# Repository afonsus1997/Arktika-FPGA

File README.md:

### Project description

The Arktika FPGA is an open-source FPGA development board based on the ICE40 family (ICE40HX4K-TQ144).

### Main Features:

* 78 total user digital IO pins
  * 18 arduino uno compatible headers
  * 6 PMOD connectors (40 total pins)
    * 2x10pin
    * 2x6pin
    * 2x4pin
  * 18pin additional "EXT" connector
  * Buzzer connector
* 4 analog input channels
  * MCP3204 ADC
* 8 on-board LEDs
* 8 on-board DIP switches
* 4 on-board push buttons
* USB to UART bridge
* 50Mhz active crystal oscillator
* FT232hl USB bridge
  * Used for FPGA or flash programming
  * Breakout header for external use

### Known bugs
* V1.0
  * Flash CS line not connected (typo on net name)
  * Arduino connector mirrores (inteded for a shield and not the arduino footprint)
  * Wrong usb to uart bridge footprint (the footprint is correct, but it is not for the intended version of the IC)

### Development Log

* 27/09/20 (up to)
  * Finishing PCB design
  * Tested toolchain with some examples

### Screenshots and pictures

### Useful development links

[ICE40 Family datasheet](https://static6.arrow.com/aropdfconversion/5a93cb52911751cf0d102889c061f1e82d924150/3ice40lphxfamilydatasheet.pdf)

[ICE40 Hardware checklist](http://www.latticesemi.com/~/media/LatticeSemi/Documents/ApplicationNotes/IK/iCE40HardwareChecklist.pdf?document_id=47779)

[ICE40 Decoupling information](https://www.latticesemi.com/-/media/LatticeSemi/Documents/ApplicationNotes/PT/PowerDecouplingandBypassFilteringforProgrammableDevices.ashx?document_id=8374)

[ICE40 Programming information](http://www.latticesemi.com/dynamic/view_document.cfm?document_id=46502)

[PMOD Standard](http://digilentinc.com/Pmods/Digilent-Pmod_%20Interface_Specification.pdf)

###### Bonus

Q: What is arktika?

A: [Glad you asked!](https://en.wikipedia.org/wiki/Arktika_(1972_icebreaker))

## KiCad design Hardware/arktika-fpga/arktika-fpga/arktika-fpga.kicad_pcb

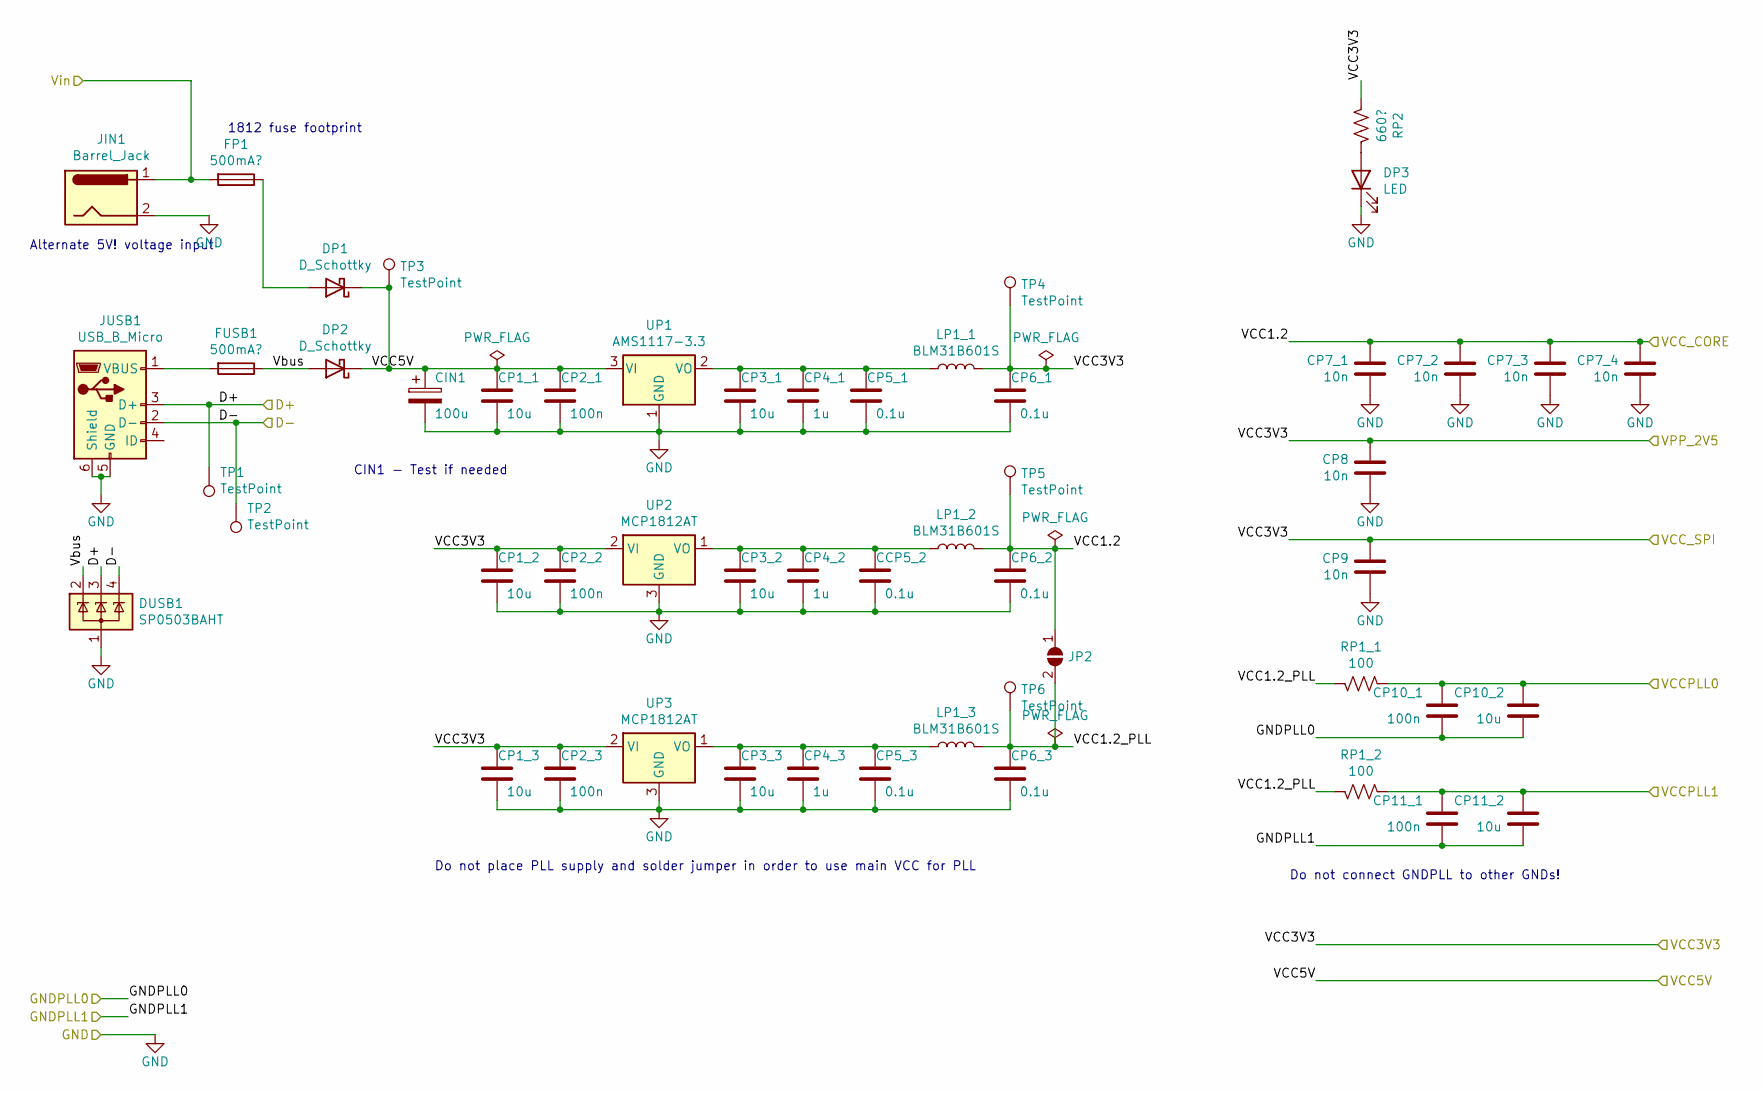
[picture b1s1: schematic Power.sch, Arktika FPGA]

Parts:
CCP5_2: 0.1u; C_0603_1608Metric_Pad1.05x0.95mm_HandSolder
CIN1: 100u; C_0603_1608Metric_Pad1.05x0.95mm_HandSolder
CP1_1, CP1_2, CP1_3, CP3_1, CP3_2, CP3_3, CP10_2, CP11_2: 10u; C_0603_1608Metric_Pad1.05x0.95mm_HandSolder
CP2_1, CP2_2, CP2_3, CP10_1, CP11_1: 100n; C_0603_1608Metric_Pad1.05x0.95mm_HandSolder
CP4_1, CP4_2, CP4_3: 1u; C_0603_1608Metric_Pad1.05x0.95mm_HandSolder
CP5_1, CP5_3, CP6_1, CP6_2, CP6_3: 0.1u; C_0603_1608Metric_Pad1.05x0.95mm_HandSolder
CP7_1, CP7_2, CP7_3, CP7_4, CP8, CP9: 10n; C_0603_1608Metric_Pad1.05x0.95mm_HandSolder
DP1, DP2: D_Schottky; D_SMA-SMB_Universal_Handsoldering
DP3: LED; LED_0603_1608Metric_Pad1.05x0.95mm_HandSolder
DUSB1: SP0503BAHT; SOT-143
FP1: 500mA?; Fuse_1812_4532Metric_Pad1.30x3.40mm_HandSolder
FUSB1: 500mA?; Fuse_1812_4532Metric_Pad1.30x3.40mm_HandSolder
JIN1: Barrel_Jack; Barrel_Jack_CUI_PJ-102AH
JP2: SolderJumper_2_Open; SolderJumper-2_P1.3mm_Open_RoundedPad1.0x1.5mm
JUSB1: USB_B_Micro; USB_Micro-B_Molex-105017-0001
LP1_1, LP1_2, LP1_3: BLM31B601S; L_1206_3216Metric_Pad1.42x1.75mm_HandSolder
RP1_1, RP1_2: 100; R_0603_1608Metric_Pad1.05x0.95mm_HandSolder
RP2: 660?; R_0603_1608Metric_Pad1.05x0.95mm_HandSolder
TP1, TP2, TP3, TP4, TP5, TP6: TestPoint; Pin_D0.7mm_L6.5mm_W1.8mm_FlatFork
UP1: AMS1117-3.3; SOT-223-3_TabPin2
UP2, UP3: MCP1812AT; SOT-23

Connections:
/D+: DUSB1.3 (K), JUSB1.3 (D+), TP1.1; also elsewhere on the board
/D-: DUSB1.4 (K), JUSB1.2 (D-), TP2.1; also elsewhere on the board
/GNDPLL0: CP11_1.2, CP11_2.2; also elsewhere on the board
/GNDPLL1: CP10_1.2, CP10_2.2; also elsewhere on the board
/Power/VCC1.2_PLL: CP6_3.1, JP2.2 (B), LP1_3.2, RP1_1.1, RP1_2.1, TP6.1
/Power/VCCPLL0: CP10_1.1, CP10_2.1, RP1_1.2; also elsewhere on the board
/Power/VCCPLL1: CP11_1.1, CP11_2.1, RP1_2.2; also elsewhere on the board
/Power/VCC_CORE: CP6_2.1, CP7_1.1, CP7_2.1, CP7_3.1, CP7_4.1, JP2.1 (A), LP1_2.2, TP5.1; also elsewhere on the board
/Power/Vbus: DP2.2 (A), DUSB1.2 (K), FUSB1.1
/VCC3V3: CP1_2.1, CP1_3.1, CP2_2.1, CP2_3.1, CP6_1.1, CP8.1, CP9.1, LP1_1.2, RP2.1, TP4.1, UP2.2 (VI), UP3.2 (VI); also elsewhere on the board
/VCC5V: CIN1.1, CP1_1.1, CP2_1.1, DP1.1 (K), DP2.1 (K), TP3.1, UP1.3 (VI); also elsewhere on the board
/VIN: FP1.2, JIN1.1; also elsewhere on the board
GND: CCP5_2.2, CIN1.2, CP1_1.2, CP1_2.2, CP1_3.2, CP2_1.2, CP2_2.2, CP2_3.2, CP3_1.2, CP3_2.2, CP3_3.2, CP4_1.2, CP4_2.2, CP4_3.2, CP5_1.2, CP5_3.2, CP6_1.2, CP6_2.2, CP6_3.2, CP7_1.2, CP7_2.2, CP7_3.2, CP7_4.2, CP8.2, CP9.2, DP3.1 (K), DUSB1.1 (A), JIN1.2, JUSB1.5 (GND), JUSB1.6 (Shield), UP1.1 (GND), UP2.3 (GND), UP3.3 (GND); also elsewhere on the board
unnamed: CCP5_2.1, CP3_2.1, CP4_2.1, LP1_2.1, UP2.1 (VO)
unnamed: CP3_1.1, CP4_1.1, CP5_1.1, LP1_1.1, UP1.2 (VO)
unnamed: CP3_3.1, CP4_3.1, CP5_3.1, LP1_3.1, UP3.1 (VO)
unnamed: DP1.2 (A), FP1.1
unnamed: DP3.2 (A), RP2.2
unnamed: FUSB1.2, JUSB1.1 (VBUS)

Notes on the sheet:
Do not connect GNDPLL to other GNDs!
Do not place PLL supply and solder jumper in order to use main VCC for PLL
CIN1 - Test if needed
Alternate 5V! voltage input
1812 fuse footprint

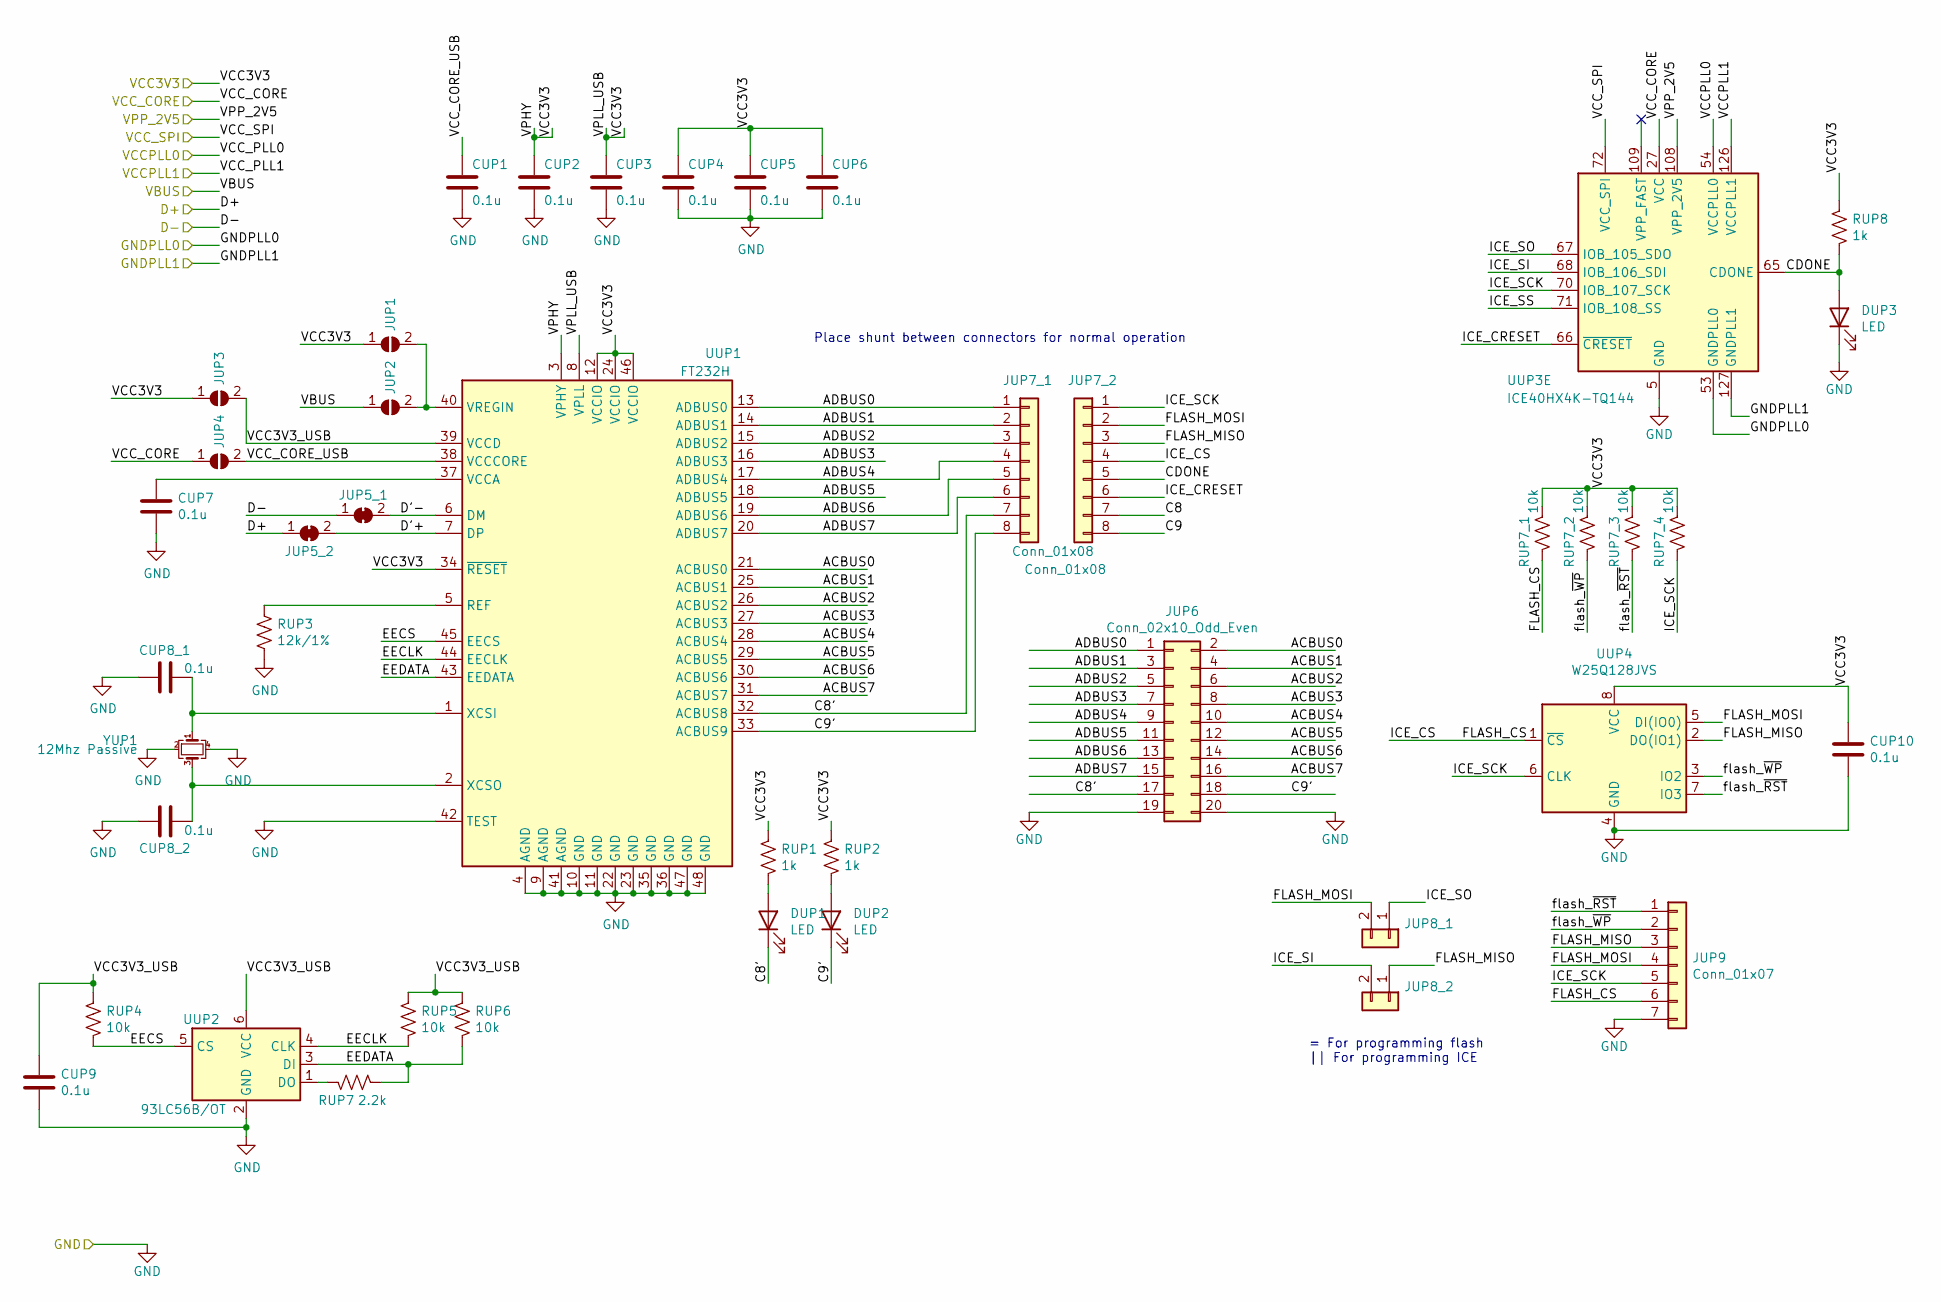
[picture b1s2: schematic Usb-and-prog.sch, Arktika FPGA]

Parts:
CUP1, CUP2, CUP3, CUP4, CUP5, CUP6, CUP7, CUP8_1, CUP8_2, CUP9, CUP10: 0.1u; C_0603_1608Metric_Pad1.05x0.95mm_HandSolder
DUP1, DUP2, DUP3: LED; LED_0603_1608Metric_Pad1.05x0.95mm_HandSolder
JUP1, JUP2, JUP3, JUP4: SolderJumper_2_Open; SolderJumper-2_P1.3mm_Open_RoundedPad1.0x1.5mm
JUP5_1, JUP5_2: SolderJumper_2_Bridged; SolderJumper-2_P1.3mm_Bridged2Bar_RoundedPad1.0x1.5mm
JUP6: Conn_02x10_Odd_Even; PinHeader_2x10_P2.54mm_Vertical
JUP7_1, JUP7_2: Conn_01x08; Pin_Header_Straight_1x08_Pitch2.54mm
JUP8_1, JUP8_2: Conn_01x02; Pin_Header_Straight_1x02_Pitch2.54mm
JUP9: Conn_01x07; PinHeader_1x07_P2.54mm_Horizontal
RUP1, RUP2, RUP8: 1k; R_0603_1608Metric_Pad1.05x0.95mm_HandSolder
RUP3: 12k/1%; R_0603_1608Metric_Pad1.05x0.95mm_HandSolder
RUP4, RUP5, RUP6, RUP7_1, RUP7_2, RUP7_3, RUP7_4: 10k; R_0603_1608Metric_Pad1.05x0.95mm_HandSolder
RUP7: 2.2k; R_0603_1608Metric_Pad1.05x0.95mm_HandSolder
UUP1: FT232H; LQFP-48-1EP_7x7mm_P0.5mm_EP3.6x3.6mm
UUP2: 93LC56B/OT; SOT-23-6_Handsoldering
UUP3: ICE40HX4K-TQ144; TQFP-144_20x20mm_P0.5mm
UUP4: W25Q128JVS; SOIC-8_3.9x4.9mm_P1.27mm
YUP1: 12Mhz Passive; Crystal_SMD_3225-4Pin_3.2x2.5mm_HandSoldering

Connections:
/D+: JUP5_2.1 (A); also elsewhere on the board
/D-: JUP5_1.1 (A); also elsewhere on the board
/GNDPLL0: UUP3.127 (GNDPLL1); also elsewhere on the board
/GNDPLL1: UUP3.53 (GNDPLL0); also elsewhere on the board
/Power/VCCPLL0: UUP3.54 (VCCPLL0); also elsewhere on the board
/Power/VCCPLL1: UUP3.126 (VCCPLL1); also elsewhere on the board
/Power/VCC_CORE: JUP4.1 (A), UUP3.27 (VCC), UUP3.40 (VCC), UUP3.92 (VCC), UUP3.111 (VCC); also elsewhere on the board
/USB AND PROG/ACBUS0: JUP6.2, UUP1.21 (ACBUS0)
/USB AND PROG/ACBUS1: JUP6.4, UUP1.25 (ACBUS1)
/USB AND PROG/ACBUS2: JUP6.6, UUP1.26 (ACBUS2)
/USB AND PROG/ACBUS3: JUP6.8, UUP1.27 (ACBUS3)
/USB AND PROG/ACBUS4: JUP6.10, UUP1.28 (ACBUS4)
/USB AND PROG/ACBUS5: JUP6.12, UUP1.29 (ACBUS5)
/USB AND PROG/ACBUS6: JUP6.14, UUP1.30 (ACBUS6)
/USB AND PROG/ACBUS7: JUP6.16, UUP1.31 (ACBUS7)
/USB AND PROG/ADBUS0: JUP6.1, JUP7_1.1, UUP1.13 (ADBUS0)
/USB AND PROG/ADBUS1: JUP6.3, JUP7_1.2, UUP1.14 (ADBUS1)
/USB AND PROG/ADBUS2: JUP6.5, JUP7_1.3, UUP1.15 (ADBUS2)
/USB AND PROG/ADBUS3: JUP6.7, UUP1.16 (ADBUS3)
/USB AND PROG/ADBUS4: JUP6.9, JUP7_1.4, UUP1.17 (ADBUS4)
/USB AND PROG/ADBUS5: JUP6.11, UUP1.18 (ADBUS5)
/USB AND PROG/ADBUS6: JUP6.13, JUP7_1.5, UUP1.19 (ADBUS6)
/USB AND PROG/ADBUS7: JUP6.15, JUP7_1.6, UUP1.20 (ADBUS7)
/USB AND PROG/C8: JUP7_2.7
/USB AND PROG/C8': DUP1.1 (K), JUP6.17, JUP7_1.7, UUP1.32 (ACBUS8)
/USB AND PROG/C9: JUP7_2.8
/USB AND PROG/C9': DUP2.1 (K), JUP6.18, JUP7_1.8, UUP1.33 (ACBUS9)
/USB AND PROG/CDONE: DUP3.2 (A), JUP7_2.5, RUP8.2, UUP3.65 (CDONE)
/USB AND PROG/D'+: JUP5_2.2 (B), UUP1.7 (DP)
/USB AND PROG/D'-: JUP5_1.2 (B), UUP1.6 (DM)
/USB AND PROG/EECLK: RUP5.2, UUP1.44 (EECLK), UUP2.4 (CLK)
/USB AND PROG/EECS: RUP4.2, UUP1.45 (EECS), UUP2.5 (CS)
/USB AND PROG/EEDATA: RUP6.2, RUP7.1, UUP1.43 (EEDATA), UUP2.3 (DI)
/USB AND PROG/FLASH_MISO: JUP7_2.3, JUP8_2.1, JUP9.3, UUP4.2 (DO(IO1))
/USB AND PROG/FLASH_MOSI: JUP7_2.2, JUP8_1.2, JUP9.4, UUP4.5 (DI(IO0))
/USB AND PROG/ICE_CRESET: JUP7_2.6, UUP3.66 (~CRESET)
/USB AND PROG/ICE_SCK: JUP7_2.1, JUP9.5, RUP7_4.2, UUP3.70 (IOB_107_SCK), UUP4.6 (CLK)
/USB AND PROG/ICE_SI: JUP8_2.2, UUP3.68 (IOB_106_SDI)
/USB AND PROG/ICE_SO: JUP8_1.1, UUP3.67 (IOB_105_SDO)
/USB AND PROG/VCC3V3_USB: CUP9.1, JUP3.2 (B), RUP4.1, RUP5.1, RUP6.1, UUP1.39 (VCCD), UUP2.6 (VCC)
/USB AND PROG/VCC_CORE_USB: CUP1.1, JUP4.2 (B), UUP1.38 (VCCCORE)
/USB AND PROG/flash_~RST: JUP9.1, RUP7_3.2, UUP4.7 (IO3)
/USB AND PROG/flash_~WP: JUP9.2, RUP7_2.2, UUP4.3 (IO2)
/VCC3V3: CUP2.1, CUP3.1, CUP4.1, CUP5.1, CUP6.1, CUP10.1, JUP1.1 (A), JUP3.1 (A), RUP1.1, RUP2.1, RUP7_1.1, RUP7_2.1, RUP7_3.1, RUP7_4.1, RUP8.1, UUP1.3 (VPHY), UUP1.8 (VPLL), UUP1.12 (VCCIO), UUP1.24 (VCCIO), UUP1.34 (~RESET), UUP1.46 (VCCIO), UUP3.72 (VCC_SPI), UUP3.108 (VPP_2V5), UUP4.8 (VCC); also elsewhere on the board
/VCC5V: JUP2.1 (A); also elsewhere on the board
GND: CUP1.2, CUP2.2, CUP3.2, CUP4.2, CUP5.2, CUP6.2, CUP7.2, CUP8_1.2, CUP8_2.2, CUP9.2, CUP10.2, DUP3.1 (K), JUP6.19, JUP6.20, JUP9.7, RUP3.2, UUP1.4 (AGND), UUP1.9 (AGND), UUP1.10 (GND), UUP1.11 (GND), UUP1.22 (GND), UUP1.23 (GND), UUP1.35 (GND), UUP1.36 (GND), UUP1.41 (AGND), UUP1.42 (TEST), UUP1.47 (GND), UUP1.48 (GND), UUP2.2 (GND), UUP3.5 (GND), UUP3.13 (GND), UUP3.14 (GND), UUP3.59 (GND), UUP3.69 (GND), UUP3.86 (GND), UUP3.103 (GND), UUP3.132 (GND), UUP3.140 (GND), UUP4.4 (GND), YUP1.2, YUP1.4; also elsewhere on the board
unnamed: CUP7.1, UUP1.37 (VCCA)
unnamed: CUP8_1.1, UUP1.1 (XCSI), YUP1.1
unnamed: CUP8_2.1, UUP1.2 (XCSO), YUP1.3
unnamed: DUP1.2 (A), RUP1.2
unnamed: DUP2.2 (A), RUP2.2
unnamed: JUP1.2 (B), JUP2.2 (B), UUP1.40 (VREGIN)
unnamed: RUP3.1, UUP1.5 (REF)
unnamed: RUP7.2, UUP2.1 (DO)

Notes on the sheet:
= For programming flash || For programming ICE
Place shunt between connectors for normal operation

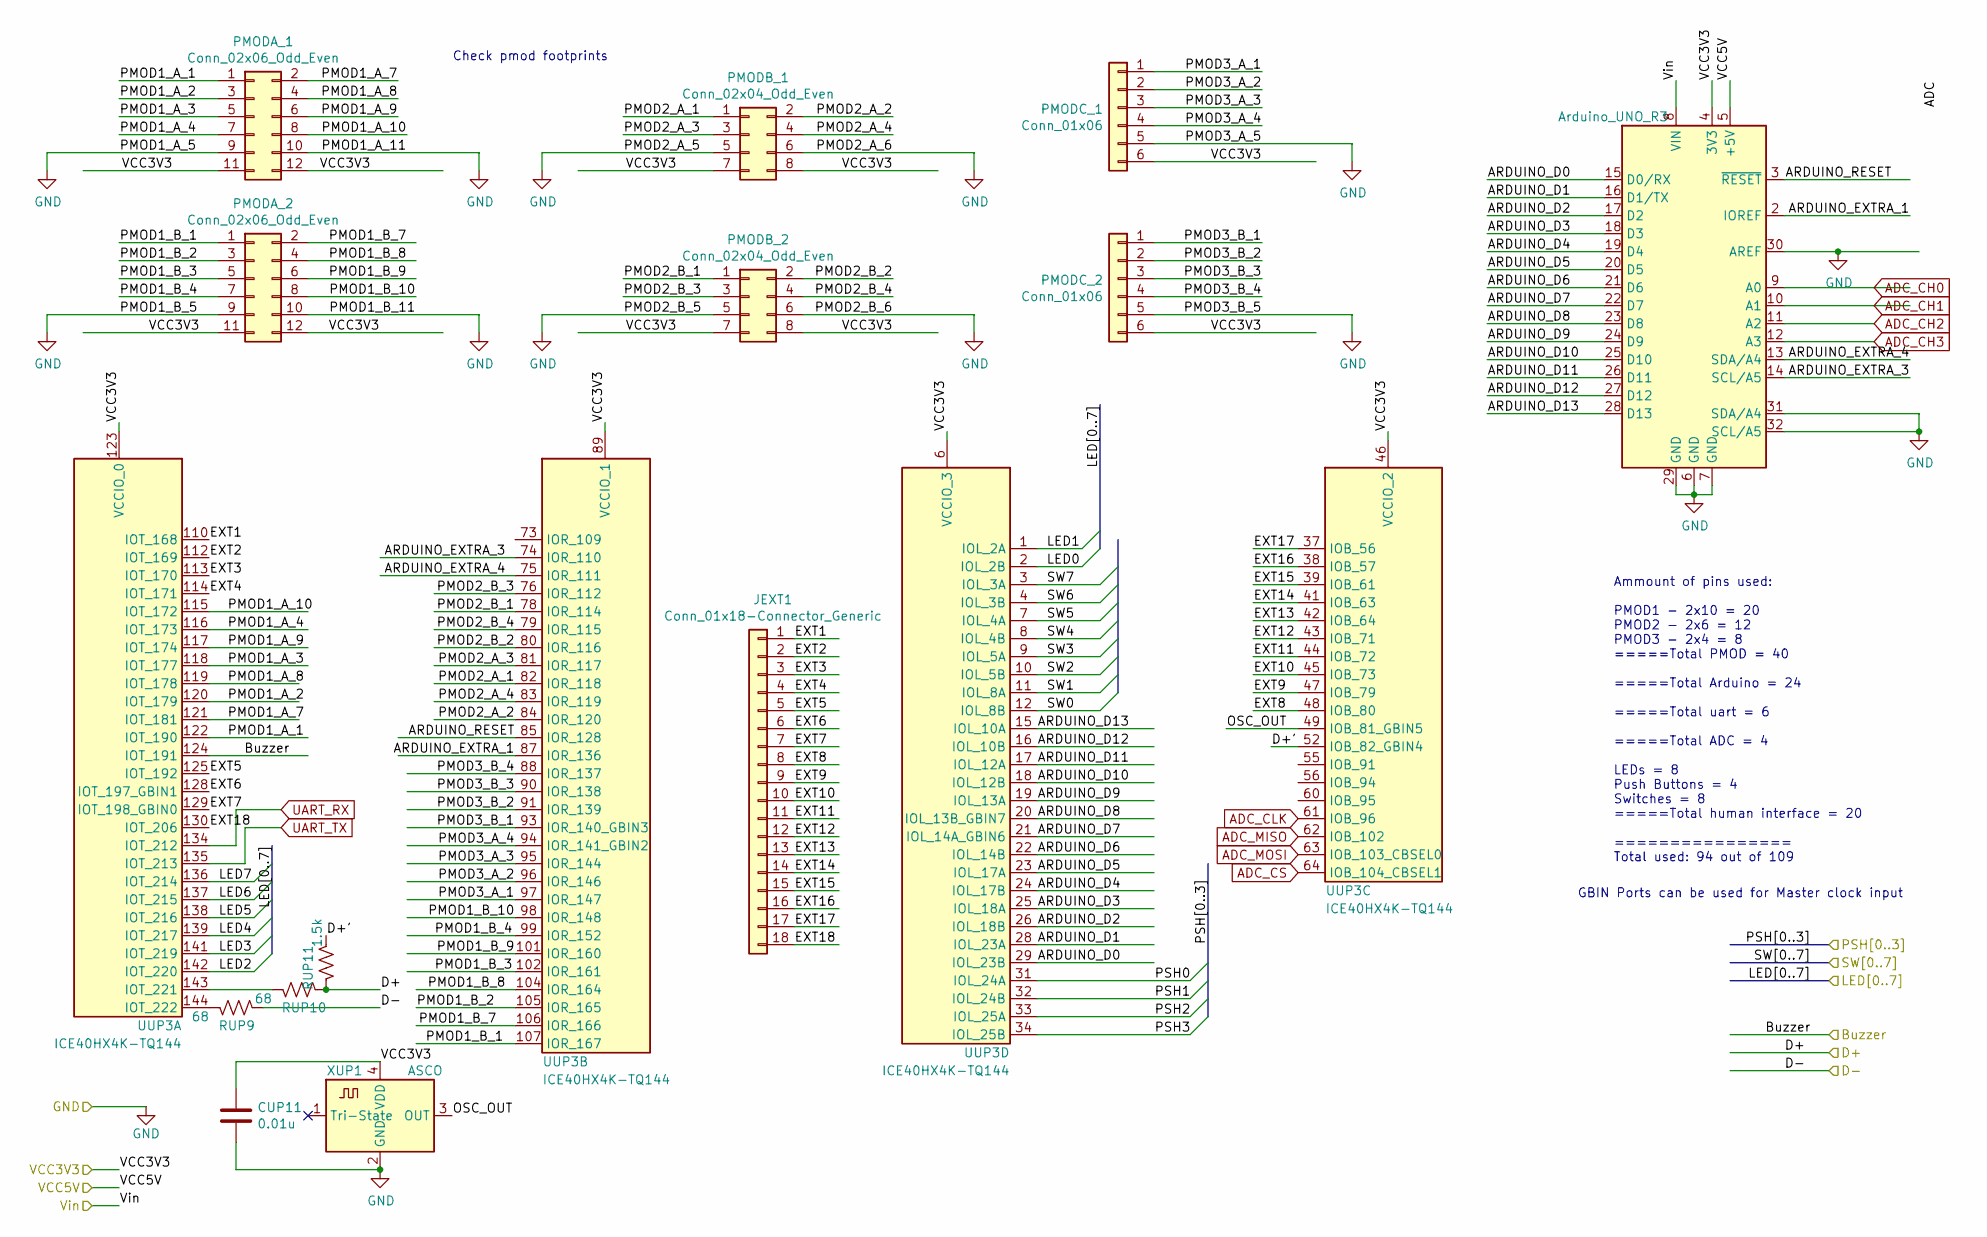
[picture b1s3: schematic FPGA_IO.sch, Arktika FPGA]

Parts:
A1: Arduino_UNO_R3
CUP11: 0.01u; C_0603_1608Metric_Pad1.05x0.95mm_HandSolder
JEXT1: Conn_01x18-Connector_Generic; PinHeader_1x18_P2.54mm_Vertical
PMODA_1, PMODA_2: Conn_02x06_Odd_Even; PinHeader_2x06_P2.54mm_Horizontal
PMODB_1, PMODB_2: Conn_02x04_Odd_Even; PinHeader_2x04_P2.54mm_Horizontal
PMODC_1, PMODC_2: Conn_01x06; PinHeader_1x06_P2.54mm_Horizontal
RUP9, RUP10: 68; R_0603_1608Metric_Pad1.05x0.95mm_HandSolder
RUP11: 1.5k; R_0603_1608Metric_Pad1.05x0.95mm_HandSolder
UUP3: ICE40HX4K-TQ144; TQFP-144_20x20mm_P0.5mm
XUP1: ASCO; Crystal_SMD_3225-4pin_3.2x2.5mm_HandSoldering

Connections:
/D+: RUP10.2, RUP11.2; also elsewhere on the board
/D-: RUP9.2; also elsewhere on the board
/FPGA_IO/ARDUINO_D0: A1.15 (D0/RX), UUP3.29 (IOL_23B)
/FPGA_IO/ARDUINO_D1: A1.16 (D1/TX), UUP3.28 (IOL_23A)
/FPGA_IO/ARDUINO_D2: A1.17 (D2), UUP3.26 (IOL_18B)
/FPGA_IO/ARDUINO_D3: A1.18 (D3), UUP3.25 (IOL_18A)
/FPGA_IO/ARDUINO_D4: A1.19 (D4), UUP3.24 (IOL_17B)
/FPGA_IO/ARDUINO_D5: A1.20 (D5), UUP3.23 (IOL_17A)
/FPGA_IO/ARDUINO_D6: A1.21 (D6), UUP3.22 (IOL_14B)
/FPGA_IO/ARDUINO_D7: A1.22 (D7), UUP3.21 (IOL_14A_GBIN6)
/FPGA_IO/ARDUINO_D8: A1.23 (D8), UUP3.20 (IOL_13B_GBIN7)
/FPGA_IO/ARDUINO_D9: A1.24 (D9), UUP3.19 (IOL_13A)
/FPGA_IO/ARDUINO_D10: A1.25 (D10), UUP3.18 (IOL_12B)
/FPGA_IO/ARDUINO_D11: A1.26 (D11), UUP3.17 (IOL_12A)
/FPGA_IO/ARDUINO_D12: A1.27 (D12), UUP3.16 (IOL_10B)
/FPGA_IO/ARDUINO_D13: A1.28 (D13), UUP3.15 (IOL_10A)
/FPGA_IO/ARDUINO_EXTRA_1: A1.2 (IOREF), UUP3.87 (IOR_136)
/FPGA_IO/ARDUINO_EXTRA_3: A1.14 (SCL/A5), UUP3.74 (IOR_110)
/FPGA_IO/ARDUINO_EXTRA_4: A1.13 (SDA/A4), UUP3.75 (IOR_111)
/FPGA_IO/ARDUINO_RESET: A1.3 (~RESET), UUP3.85 (IOR_128)
/FPGA_IO/Buzzer: UUP3.124 (IOT_191); also elsewhere on the board
/FPGA_IO/D+': RUP11.1, UUP3.52 (IOB_82_GBIN4)
/FPGA_IO/EXT1: JEXT1.1, UUP3.110 (IOT_168)
/FPGA_IO/EXT2: JEXT1.2, UUP3.112 (IOT_169)
/FPGA_IO/EXT3: JEXT1.3, UUP3.113 (IOT_170)
/FPGA_IO/EXT4: JEXT1.4, UUP3.114 (IOT_171)
/FPGA_IO/EXT5: JEXT1.5, UUP3.125 (IOT_192)
/FPGA_IO/EXT6: JEXT1.6, UUP3.128 (IOT_197_GBIN1)
/FPGA_IO/EXT7: JEXT1.7, UUP3.129 (IOT_198_GBIN0)
/FPGA_IO/EXT8: JEXT1.8, UUP3.48 (IOB_80)
/FPGA_IO/EXT9: JEXT1.9, UUP3.47 (IOB_79)
/FPGA_IO/EXT10: JEXT1.10, UUP3.45 (IOB_73)
/FPGA_IO/EXT11: JEXT1.11, UUP3.44 (IOB_72)
/FPGA_IO/EXT12: JEXT1.12, UUP3.43 (IOB_71)
/FPGA_IO/EXT13: JEXT1.13, UUP3.42 (IOB_64)
/FPGA_IO/EXT14: JEXT1.14, UUP3.41 (IOB_63)
/FPGA_IO/EXT15: JEXT1.15, UUP3.39 (IOB_61)
/FPGA_IO/EXT16: JEXT1.16, UUP3.38 (IOB_57)
/FPGA_IO/EXT17: JEXT1.17, UUP3.37 (IOB_56)
/FPGA_IO/EXT18: JEXT1.18, UUP3.130 (IOT_206)
/FPGA_IO/LED0: UUP3.2 (IOL_2B); also elsewhere on the board
/FPGA_IO/LED1: UUP3.1 (IOL_2A); also elsewhere on the board
/FPGA_IO/LED2: UUP3.142 (IOT_220); also elsewhere on the board
/FPGA_IO/LED3: UUP3.141 (IOT_219); also elsewhere on the board
/FPGA_IO/LED4: UUP3.139 (IOT_217); also elsewhere on the board
/FPGA_IO/LED5: UUP3.138 (IOT_216); also elsewhere on the board
/FPGA_IO/LED6: UUP3.137 (IOT_215); also elsewhere on the board
/FPGA_IO/LED7: UUP3.136 (IOT_214); also elsewhere on the board
/FPGA_IO/OSC_OUT: UUP3.49 (IOB_81_GBIN5), XUP1.3 (OUT)
/FPGA_IO/PMOD1_A_1: PMODA_1.1, UUP3.122 (IOT_190)
/FPGA_IO/PMOD1_A_2: PMODA_1.3, UUP3.120 (IOT_179)
/FPGA_IO/PMOD1_A_3: PMODA_1.5, UUP3.118 (IOT_177)
/FPGA_IO/PMOD1_A_4: PMODA_1.7, UUP3.116 (IOT_173)
/FPGA_IO/PMOD1_A_7: PMODA_1.2, UUP3.121 (IOT_181)
/FPGA_IO/PMOD1_A_8: PMODA_1.4, UUP3.119 (IOT_178)
/FPGA_IO/PMOD1_A_9: PMODA_1.6, UUP3.117 (IOT_174)
/FPGA_IO/PMOD1_A_10: PMODA_1.8, UUP3.115 (IOT_172)
/FPGA_IO/PMOD1_B_1: PMODA_2.1, UUP3.107 (IOR_167)
/FPGA_IO/PMOD1_B_2: PMODA_2.3, UUP3.105 (IOR_165)
/FPGA_IO/PMOD1_B_3: PMODA_2.5, UUP3.102 (IOR_161)
/FPGA_IO/PMOD1_B_4: PMODA_2.7, UUP3.99 (IOR_152)
/FPGA_IO/PMOD1_B_7: PMODA_2.2, UUP3.106 (IOR_166)
/FPGA_IO/PMOD1_B_8: PMODA_2.4, UUP3.104 (IOR_164)
/FPGA_IO/PMOD1_B_9: PMODA_2.6, UUP3.101 (IOR_160)
/FPGA_IO/PMOD1_B_10: PMODA_2.8, UUP3.98 (IOR_148)
/FPGA_IO/PMOD2_A_1: PMODB_1.1, UUP3.82 (IOR_118)
/FPGA_IO/PMOD2_A_2: PMODB_1.2, UUP3.84 (IOR_120)
/FPGA_IO/PMOD2_A_3: PMODB_1.3, UUP3.81 (IOR_117)
/FPGA_IO/PMOD2_A_4: PMODB_1.4, UUP3.83 (IOR_119)
/FPGA_IO/PMOD2_B_1: PMODB_2.1, UUP3.78 (IOR_114)
/FPGA_IO/PMOD2_B_2: PMODB_2.2, UUP3.80 (IOR_116)
/FPGA_IO/PMOD2_B_3: PMODB_2.3, UUP3.76 (IOR_112)
/FPGA_IO/PMOD2_B_4: PMODB_2.4, UUP3.79 (IOR_115)
/FPGA_IO/PMOD3_A_1: PMODC_1.1, UUP3.97 (IOR_147)
/FPGA_IO/PMOD3_A_2: PMODC_1.2, UUP3.96 (IOR_146)
/FPGA_IO/PMOD3_A_3: PMODC_1.3, UUP3.95 (IOR_144)
/FPGA_IO/PMOD3_A_4: PMODC_1.4, UUP3.94 (IOR_141_GBIN2)
/FPGA_IO/PMOD3_B_1: PMODC_2.1, UUP3.93 (IOR_140_GBIN3)
/FPGA_IO/PMOD3_B_2: PMODC_2.2, UUP3.91 (IOR_139)
/FPGA_IO/PMOD3_B_3: PMODC_2.3, UUP3.90 (IOR_138)
/FPGA_IO/PMOD3_B_4: PMODC_2.4, UUP3.88 (IOR_137)
/FPGA_IO/PSH0: UUP3.31 (IOL_24A); also elsewhere on the board
/FPGA_IO/PSH1: UUP3.32 (IOL_24B); also elsewhere on the board
/FPGA_IO/PSH2: UUP3.33 (IOL_25A); also elsewhere on the board
/FPGA_IO/PSH3: UUP3.34 (IOL_25B); also elsewhere on the board
/FPGA_IO/SW0: UUP3.12 (IOL_8B); also elsewhere on the board
/FPGA_IO/SW1: UUP3.11 (IOL_8A); also elsewhere on the board
/FPGA_IO/SW2: UUP3.10 (IOL_5B); also elsewhere on the board
/FPGA_IO/SW3: UUP3.9 (IOL_5A); also elsewhere on the board
/FPGA_IO/SW4: UUP3.8 (IOL_4B); also elsewhere on the board
/FPGA_IO/SW5: UUP3.7 (IOL_4A); also elsewhere on the board
/FPGA_IO/SW6: UUP3.4 (IOL_3B); also elsewhere on the board
/FPGA_IO/SW7: UUP3.3 (IOL_3A); also elsewhere on the board
/VCC3V3: A1.4 (3V3), CUP11.1, PMODA_1.11, PMODA_1.12, PMODA_2.11, PMODA_2.12, PMODB_1.7, PMODB_1.8, PMODB_2.7, PMODB_2.8, PMODC_1.6, PMODC_2.6, UUP3.6 (VCCIO_3), UUP3.30 (VCCIO_3), UUP3.46 (VCCIO_2), UUP3.57 (VCCIO_2), UUP3.89 (VCCIO_1), UUP3.100 (VCCIO_1), UUP3.123 (VCCIO_0), UUP3.131 (VCCIO_0), XUP1.4 (VDD); also elsewhere on the board
/VCC5V: A1.5 (+5V); also elsewhere on the board
/VIN: A1.8 (VIN); also elsewhere on the board
ADC_CH0: A1.9 (A0); also elsewhere on the board
ADC_CH1: A1.10 (A1); also elsewhere on the board
ADC_CH2: A1.11 (A2); also elsewhere on the board
ADC_CH3: A1.12 (A3); also elsewhere on the board
ADC_CLK: UUP3.61 (IOB_96); also elsewhere on the board
ADC_CS: UUP3.64 (IOB_104_CBSEL1); also elsewhere on the board
ADC_MISO: UUP3.62 (IOB_102); also elsewhere on the board
ADC_MOSI: UUP3.63 (IOB_103_CBSEL0); also elsewhere on the board
GND: A1.6 (GND), A1.7 (GND), A1.29 (GND), A1.30 (AREF), A1.31 (SDA/A4), A1.32 (SCL/A5), CUP11.2, PMODA_1.9, PMODA_1.10, PMODA_2.9, PMODA_2.10, PMODB_1.5, PMODB_1.6, PMODB_2.5, PMODB_2.6, PMODC_1.5, PMODC_2.5, XUP1.2 (GND); also elsewhere on the board
unnamed: RUP9.1, UUP3.144 (IOT_222)
unnamed: RUP10.1, UUP3.143 (IOT_221)
UART_RX: UUP3.134 (IOT_212); also elsewhere on the board
UART_TX: UUP3.135 (IOT_213); also elsewhere on the board

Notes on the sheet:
Ammount of pins used: PMOD1 - 2x10 = 20 PMOD2 - 2x6 = 12 PMOD3 - 2x4 = 8 =====Total PMOD = 40 =====Total Arduino = 24 =====Total uart = 6 =====Total ADC = 4 LEDs = 8 Push Buttons = 4 Switches = 8 =====Total human interface = 20 ================ Total used: 94 out of 109
GBIN Ports can be used for Master clock input
Check pmod footprints

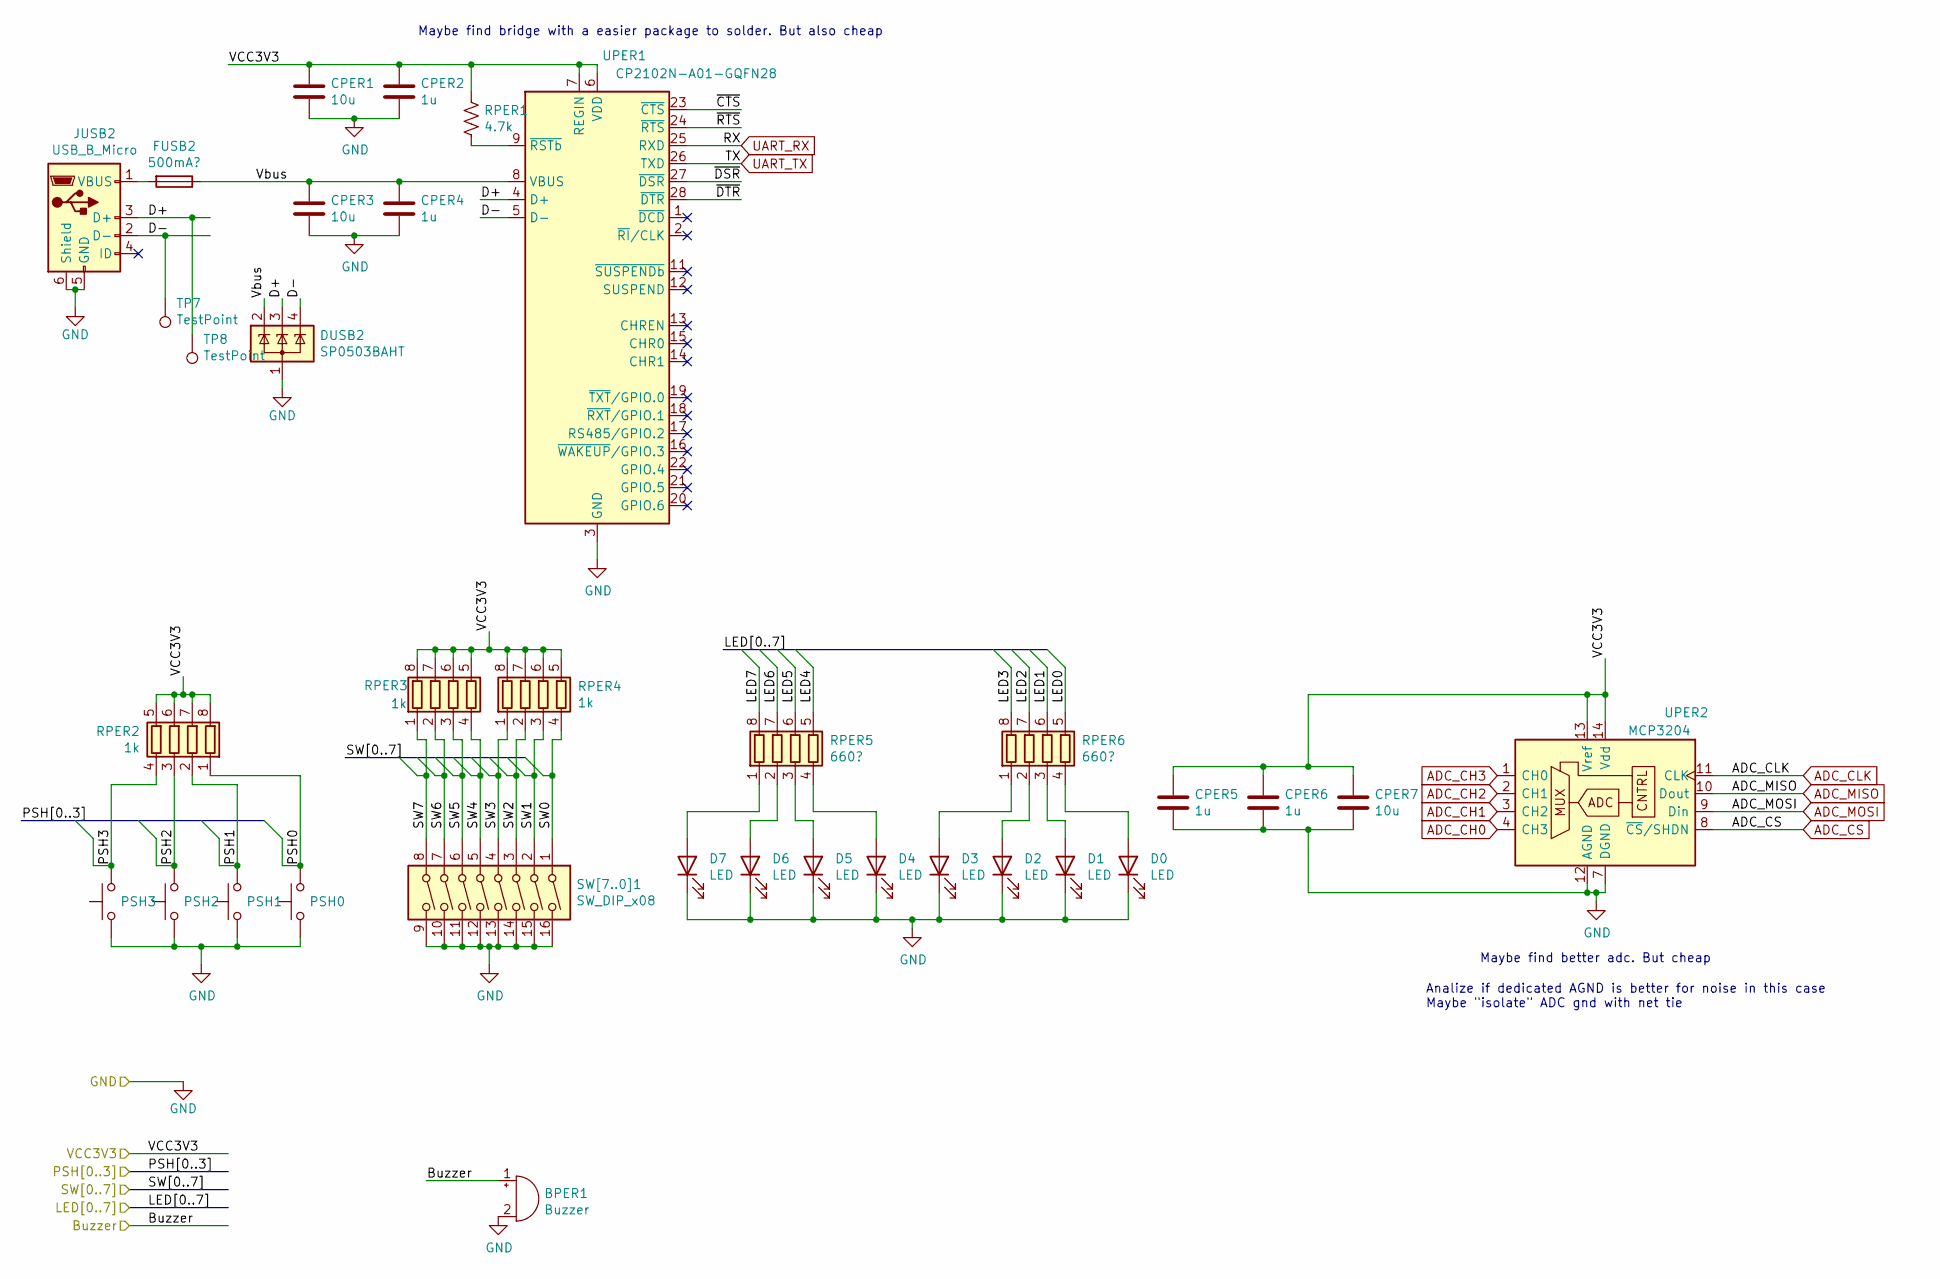
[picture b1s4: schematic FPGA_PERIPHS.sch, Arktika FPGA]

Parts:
BPER1: Buzzer; PinHeader_1x02_P2.54mm_Vertical
CPER1, CPER3, CPER7: 10u; C_0603_1608Metric_Pad1.05x0.95mm_HandSolder
CPER2, CPER4, CPER5, CPER6: 1u; C_0603_1608Metric_Pad1.05x0.95mm_HandSolder
D0, D1, D2, D3, D4, D5, D6, D7: LED; LED_0603_1608Metric_Pad1.05x0.95mm_HandSolder
DUSB2: SP0503BAHT; SOT-143
FUSB2: 500mA?; Fuse_1812_4532Metric_Pad1.30x3.40mm_HandSolder
JUSB2: USB_B_Micro; USB_Micro-B_Molex-105017-0001
PSH0, PSH1, PSH2, PSH3: SW_Push; SW_SPST_PTS645
RPER1: 4.7k; R_0603_1608Metric_Pad1.05x0.95mm_HandSolder
RPER2, RPER3, RPER4: 1k; R_Array_Convex_4x0603
RPER5, RPER6: 660?; R_Array_Convex_4x0603
SW[7..0]1: SW_DIP_x08; SW_DIP_SPSTx08_Slide_6.7x21.88mm_W8.61mm_P2.54mm_LowProfile
TP7, TP8: TestPoint; Pin_D0.7mm_L6.5mm_W1.8mm_FlatFork
UPER1: CP2102N-A01-GQFN28; QFN-28-1EP_4x4mm_P0.4mm_EP2.6x2.6mm
UPER2: MCP3204; SOIC-14_3.9x8.7mm_P1.27mm

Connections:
/FPGA_IO/Buzzer: BPER1.1 (-); also elsewhere on the board
/FPGA_IO/LED0: RPER6.5 (R4.2); also elsewhere on the board
/FPGA_IO/LED1: RPER6.6 (R3.2); also elsewhere on the board
/FPGA_IO/LED2: RPER6.7 (R2.2); also elsewhere on the board
/FPGA_IO/LED3: RPER6.8 (R1.2); also elsewhere on the board
/FPGA_IO/LED4: RPER5.5 (R4.2); also elsewhere on the board
/FPGA_IO/LED5: RPER5.6 (R3.2); also elsewhere on the board
/FPGA_IO/LED6: RPER5.7 (R2.2); also elsewhere on the board
/FPGA_IO/LED7: RPER5.8 (R1.2); also elsewhere on the board
/FPGA_IO/PSH0: PSH0.2, RPER2.1 (R1.1); also elsewhere on the board
/FPGA_IO/PSH1: PSH1.2, RPER2.2 (R2.1); also elsewhere on the board
/FPGA_IO/PSH2: PSH2.2, RPER2.3 (R3.1); also elsewhere on the board
/FPGA_IO/PSH3: PSH3.2, RPER2.4 (R4.1); also elsewhere on the board
/FPGA_IO/SW0: RPER4.4 (R4.1), SW[7..0]1.1; also elsewhere on the board
/FPGA_IO/SW1: RPER4.3 (R3.1), SW[7..0]1.2; also elsewhere on the board
/FPGA_IO/SW2: RPER4.2 (R2.1), SW[7..0]1.3; also elsewhere on the board
/FPGA_IO/SW3: RPER4.1 (R1.1), SW[7..0]1.4; also elsewhere on the board
/FPGA_IO/SW4: RPER3.4 (R4.1), SW[7..0]1.5; also elsewhere on the board
/FPGA_IO/SW5: RPER3.3 (R3.1), SW[7..0]1.6; also elsewhere on the board
/FPGA_IO/SW6: RPER3.2 (R2.1), SW[7..0]1.7; also elsewhere on the board
/FPGA_IO/SW7: RPER3.1 (R1.1), SW[7..0]1.8; also elsewhere on the board
/FPGA_PERIPHS/D+: DUSB2.3 (K), JUSB2.3 (D+), TP8.1, UPER1.4 (D+)
/FPGA_PERIPHS/D-: DUSB2.4 (K), JUSB2.2 (D-), TP7.1, UPER1.5 (D-)
/FPGA_PERIPHS/Vbus: CPER3.1, CPER4.1, DUSB2.2 (K), FUSB2.1, UPER1.8 (VBUS)
/FPGA_PERIPHS/~CTS: UPER1.23 (~CTS)
/FPGA_PERIPHS/~DSR: UPER1.27 (~DSR)
/FPGA_PERIPHS/~DTR: UPER1.28 (~DTR)
/FPGA_PERIPHS/~RTS: UPER1.24 (~RTS)
/VCC3V3: CPER1.1, CPER2.1, CPER5.1, CPER6.1, CPER7.1, RPER1.1, RPER2.5 (R4.2), RPER2.6 (R3.2), RPER2.7 (R2.2), RPER2.8 (R1.2), RPER3.5 (R4.2), RPER3.6 (R3.2), RPER3.7 (R2.2), RPER3.8 (R1.2), RPER4.5 (R4.2), RPER4.6 (R3.2), RPER4.7 (R2.2), RPER4.8 (R1.2), UPER1.6 (VDD), UPER1.7 (REGIN), UPER2.13 (Vref), UPER2.14 (Vdd); also elsewhere on the board
ADC_CH0: UPER2.4 (CH3); also elsewhere on the board
ADC_CH1: UPER2.3 (CH2); also elsewhere on the board
ADC_CH2: UPER2.2 (CH1); also elsewhere on the board
ADC_CH3: UPER2.1 (CH0); also elsewhere on the board
ADC_CLK: UPER2.11 (CLK); also elsewhere on the board
ADC_CS: UPER2.8 (~CS~/SHDN); also elsewhere on the board
ADC_MISO: UPER2.10 (Dout); also elsewhere on the board
ADC_MOSI: UPER2.9 (Din); also elsewhere on the board
GND: BPER1.2 (+), CPER1.2, CPER2.2, CPER3.2, CPER4.2, CPER5.2, CPER6.2, CPER7.2, D0.1 (K), D1.1 (K), D2.1 (K), D3.1 (K), D4.1 (K), D5.1 (K), D6.1 (K), D7.1 (K), DUSB2.1 (A), JUSB2.5 (GND), JUSB2.6 (Shield), PSH0.1, PSH1.1, PSH2.1, PSH3.1, SW[7..0]1.9, SW[7..0]1.10, SW[7..0]1.11, SW[7..0]1.12, SW[7..0]1.13, SW[7..0]1.14, SW[7..0]1.15, SW[7..0]1.16, UPER1.3 (GND), UPER1.29 (GND), UPER2.7 (DGND), UPER2.12 (AGND); also elsewhere on the board
unnamed: D0.2 (A), RPER6.4 (R4.1)
unnamed: D1.2 (A), RPER6.3 (R3.1)
unnamed: D2.2 (A), RPER6.2 (R2.1)
unnamed: D3.2 (A), RPER6.1 (R1.1)
unnamed: D4.2 (A), RPER5.4 (R4.1)
unnamed: D5.2 (A), RPER5.3 (R3.1)
unnamed: D6.2 (A), RPER5.2 (R2.1)
unnamed: D7.2 (A), RPER5.1 (R1.1)
unnamed: FUSB2.2, JUSB2.1 (VBUS)
unnamed: RPER1.2, UPER1.9 (~RSTb)
UART_RX: UPER1.25 (RXD); also elsewhere on the board
UART_TX: UPER1.26 (TXD); also elsewhere on the board

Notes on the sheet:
Maybe find better adc. But cheap
Maybe find bridge with a easier package to solder. But also cheap
Analize if dedicated AGND is better for noise in this case Maybe "isolate" ADC gnd with net tie

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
